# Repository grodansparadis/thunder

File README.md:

# thunder
wifi + ethernet for VSCP

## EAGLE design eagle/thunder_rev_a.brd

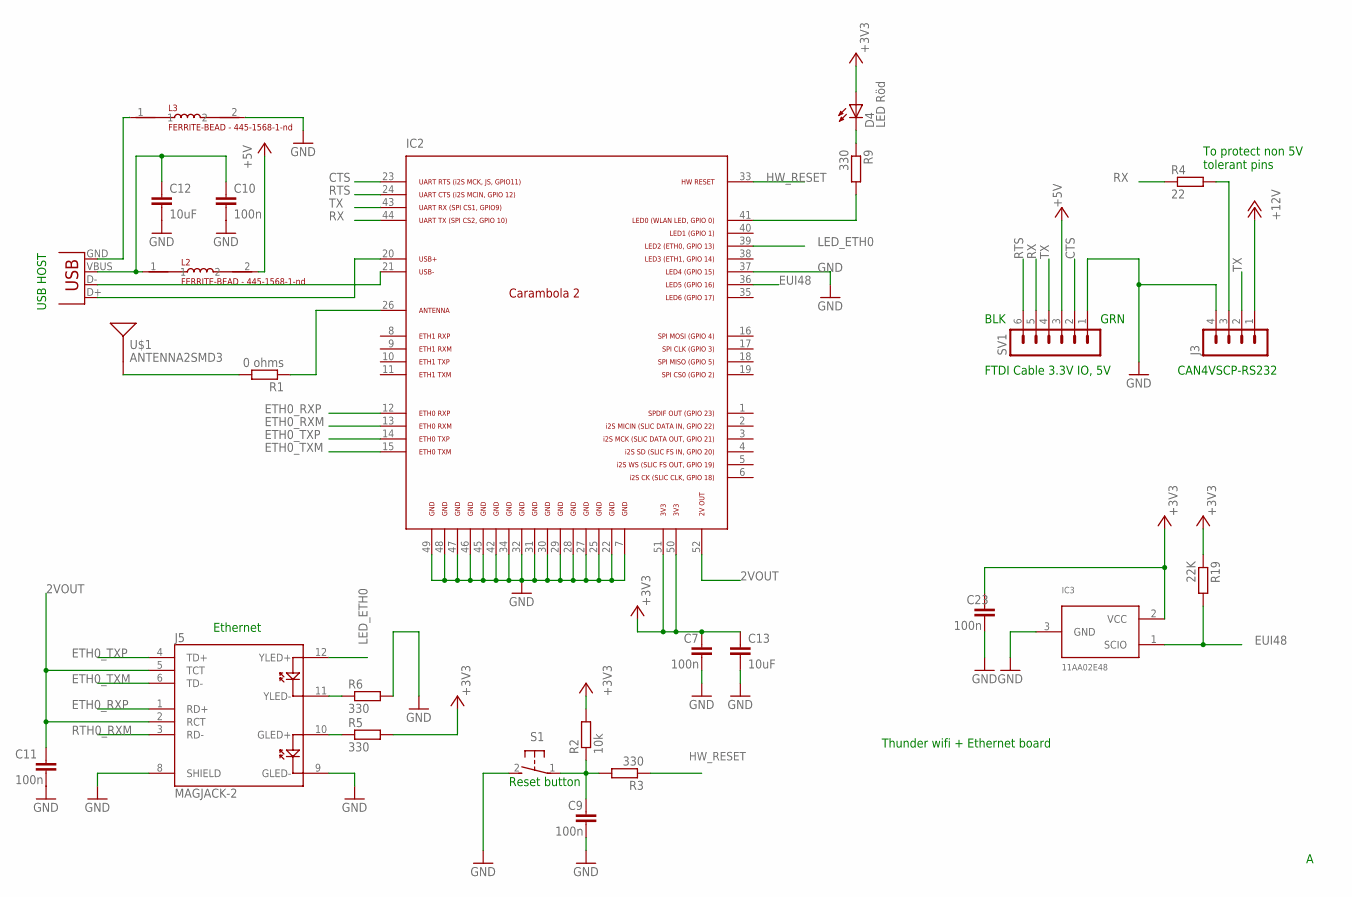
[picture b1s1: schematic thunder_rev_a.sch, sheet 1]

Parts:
C7, C9, C10, C11, C23: 100n; C0805
C12, C13: 10uF; C0805
D4: LED Röd; C2012
IC2: CARAMBOLA2
IC3: 11AA02E48; SOT23
J3: MA04-1
J5: MAGJACK-2; MAGJACK-19938
JP1: USB-A-SMD; USB-A-S-NOSILK-FEMALE
L2, L3: FERRITE-BEAD - 445-1568-1-nd; 0805
R1: 0 ohms; M0805
R2: 10k; M0805
R3, R5, R6, R9: 330; M0805
R4: 22; M0805
R19: 22K; M0805
S1: 31-XX; B3F-31XX
SV1: MA06-1
U$1: ANTENNA2SMD3; ANTENNA-CHIP4

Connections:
2VOUT: C11.1, IC2.52, J5.2 (RCT), J5.5 (TCT)
22: IC2.7, IC2.22, IC2.25, IC2.27, IC2.28, IC2.29, IC2.30, IC2.31, IC2.32, IC2.34, IC2.42, IC2.45, IC2.46, IC2.47, IC2.48, IC2.49
50: C7.1, C13.1, IC2.50, IC2.51
+3V3: C23.1, D4.1 (A), IC3.2 (VCC), R2.2, R5.2, R19.1; also elsewhere on the board
+5V: L2.2, SV1.3; also elsewhere on the board
+12V: J3.1; also elsewhere on the board
CTS: IC2.23, SV1.2
ETH0_RXM: IC2.13
ETH0_RXP: IC2.12, J5.1 (RD+)
ETH0_TXM: IC2.15, J5.6 (TD-)
ETH0_TXP: IC2.14, J5.4 (TD+)
EUI48: IC2.36, IC3.1 (SCIO), R19.2
GND: C7.2, C9.2, C10.2, C11.2, C12.2, C13.2, C23.2, IC2.37, IC3.3 (GND), J3.4, J5.8 (SHIELD), J5.9 (GLED-), L3.2, R6.2, S1.2 (S), SV1.1; also elsewhere on the board
HW_RESET: IC2.33, R3.1
LED_ETH0: IC2.39, J5.12 (YLED+)
unnamed: C9.1, R2.1, R3.2, S1.1
unnamed: IC2.41, R9.2
unnamed: J5.10 (GLED+), R5.1
unnamed: IC2.21, JP1.D-
unnamed: J5.11 (YLED-), R6.1
unnamed: R1.2, U$1.SIG
unnamed: IC2.26, R1.1
unnamed: J3.3, R4.2
unnamed: D4.2 (C), R9.1
unnamed: IC2.20, JP1.D+
unnamed: C10.1, C12.1, JP1.VBUS, L2.1
unnamed: JP1.GND, L3.1
RTH0_RXM: J5.3 (RD-)
RTS: IC2.24, SV1.6
RX: IC2.44, R4.1, SV1.5
TX: IC2.43, J3.2, SV1.4

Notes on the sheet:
Thunder wifi + Ethernet board
FTDI Cable 3.3V IO, 5V
GRN
BLK
USB HOST
CAN4VSCP-RS232
Ethernet
To protect non 5V tolerant pins
Reset button

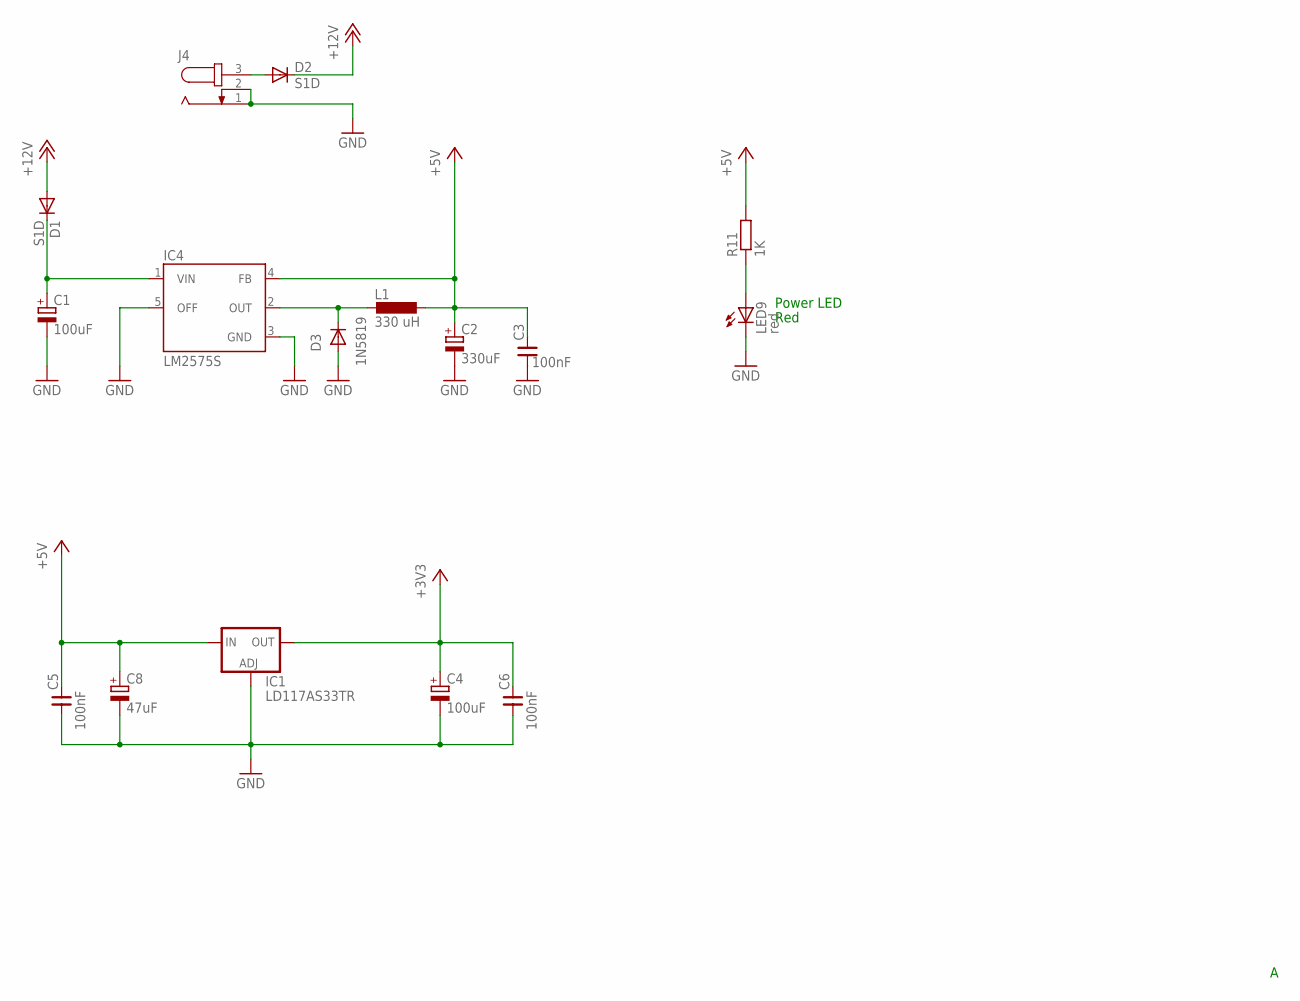
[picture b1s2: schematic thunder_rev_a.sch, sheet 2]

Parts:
C1, C4: 100uF; PANASONIC_D
C2: 330uF; PANASONIC_D
C3, C5, C6: 100nF; 0805
C8: 47uF; PANASONIC_D
D1: S1D; SOD123
D2: S1D; SMB
D3: 1N5819; SOD123
IC1: LD117AS33TR; SOT223
IC4: LM2575S; TO263-5
J4: JACK-PLUG0; SPC4077
L1: 330 uH; DO3316P
LED9: red; CHIP-LED0805
R11: 1K; R0805

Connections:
+3V3: C4.+, C6.2, IC1.4 (OUT); also elsewhere on the board
+5V: C2.+, C3.2, C5.2, C8.+, IC1.3 (IN), IC4.4 (FB), L1.2, R11.2; also elsewhere on the board
+12V: D1.A, D2.C; also elsewhere on the board
GND: C1.-, C2.-, C3.1, C4.-, C5.1, C6.1, C8.-, D3.A, IC1.1 (ADJ), IC4.3 (GND), IC4.5 (OFF), J4.1, J4.2, LED9.C; also elsewhere on the board
unnamed: D3.C, IC4.2 (OUT), L1.1
unnamed: C1.+, D1.C, IC4.1 (VIN)
unnamed: D2.A, J4.3
unnamed: LED9.A, R11.1

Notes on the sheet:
Power LED
Red

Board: 2 copper layers, 42 parts (0 on the bottom side), 33 nets, no tracks yet.

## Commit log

2015-08-28 Moved from private to public

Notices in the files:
parts and their libraries:
SparkFun-Connectors: Licensing: Creative Commons ShareAlike 4.0 International - https://creativecommons.org/licenses/by-sa/4.0
